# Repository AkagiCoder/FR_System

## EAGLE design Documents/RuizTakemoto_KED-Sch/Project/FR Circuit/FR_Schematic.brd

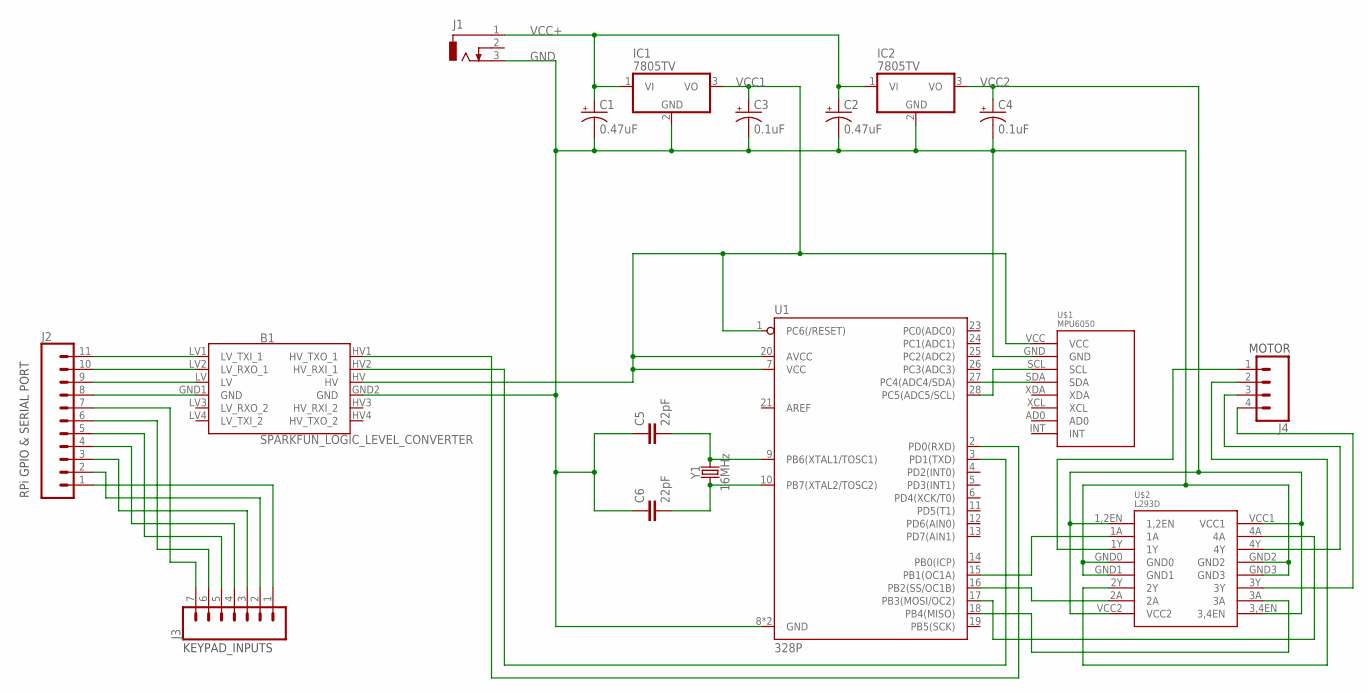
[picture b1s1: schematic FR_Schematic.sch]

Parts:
B1: SPARKFUN_LOGIC_LEVEL_CONVERTER
C1, C2: 0.47uF; CPOL-RADIAL-2.5MM-5MM
C3, C4: 0.1uF; E1,8-4
C5, C6: 22pF; CAP-PTH-2.54
IC1, IC2: 7805TV; TO220V
J1: DCJ0303
J2: CONN_11; 1X11
J3: CONN_07; 1X07
J4: CONN_04PTH; 1X04
U1: 328P; DIP28
U$1: MPU6050
U$2: L293D
Y1: 16MHz; HC49US

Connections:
GND: B1.GND2 (GND), C1.2 (-), C2.2 (-), C3.-, C4.-, C5.1, C6.1, IC1.2 (GND), IC2.2 (GND), J1.3, U1.8 (GND), U1.22 (GND), U$1.GND, U$2.GND0, U$2.GND1, U$2.GND2, U$2.GND3
unnamed: B1.HV1 (HV_TXO_1), U1.2 (PD0(RXD))
unnamed: B1.HV2 (HV_RXI_1), U1.3 (PD1(TXD))
unnamed: B1.LV1 (LV_TXI_1), J2.11
unnamed: B1.LV2 (LV_RXO_1), J2.10
unnamed: C6.2, U1.10 (PB7(XTAL2/TOSC2)), Y1.1
unnamed: C5.2, U1.9 (PB6(XTAL1/TOSC1)), Y1.2
unnamed: B1.LV, J2.9
unnamed: B1.GND1 (GND), J2.8
unnamed: J2.7, J3.7
unnamed: J2.6, J3.6
unnamed: J2.5, J3.5
unnamed: J2.4, J3.4
unnamed: J2.3, J3.3
unnamed: J2.2, J3.2
unnamed: J2.1, J3.1
unnamed: U1.27 (PC4(ADC4/SDA)), U$1.SDA
unnamed: U1.28 (PC5(ADC5/SCL)), U$1.SCL
unnamed: U1.15 (PB1(OC1A)), U$2.1A
unnamed: U1.16 (PB2(SS/OC1B)), U$2.2A
unnamed: U1.17 (PB3(MOSI/OC2)), U$2.4A
unnamed: U1.18 (PB4(MISO)), U$2.3A
unnamed: J4.1, U$2.1Y
unnamed: J4.2, U$2.2Y
unnamed: J4.3, U$2.4Y
unnamed: J4.4, U$2.3Y
VCC1: B1.HV, C3.+, IC1.3 (VO), U1.1 (PC6(/RESET)), U1.7 (VCC), U1.20 (AVCC), U$1.VCC
VCC2: C4.+, IC2.3 (VO), U$2.1,2EN, U$2.3,4EN, U$2.VCC1, U$2.VCC2
VCC+: C1.1 (+), C2.1 (+), IC1.1 (VI), IC2.1 (VI), J1.1

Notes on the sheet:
KEYPAD_INPUTS
RPi GPIO & SERIAL PORT
MOTOR

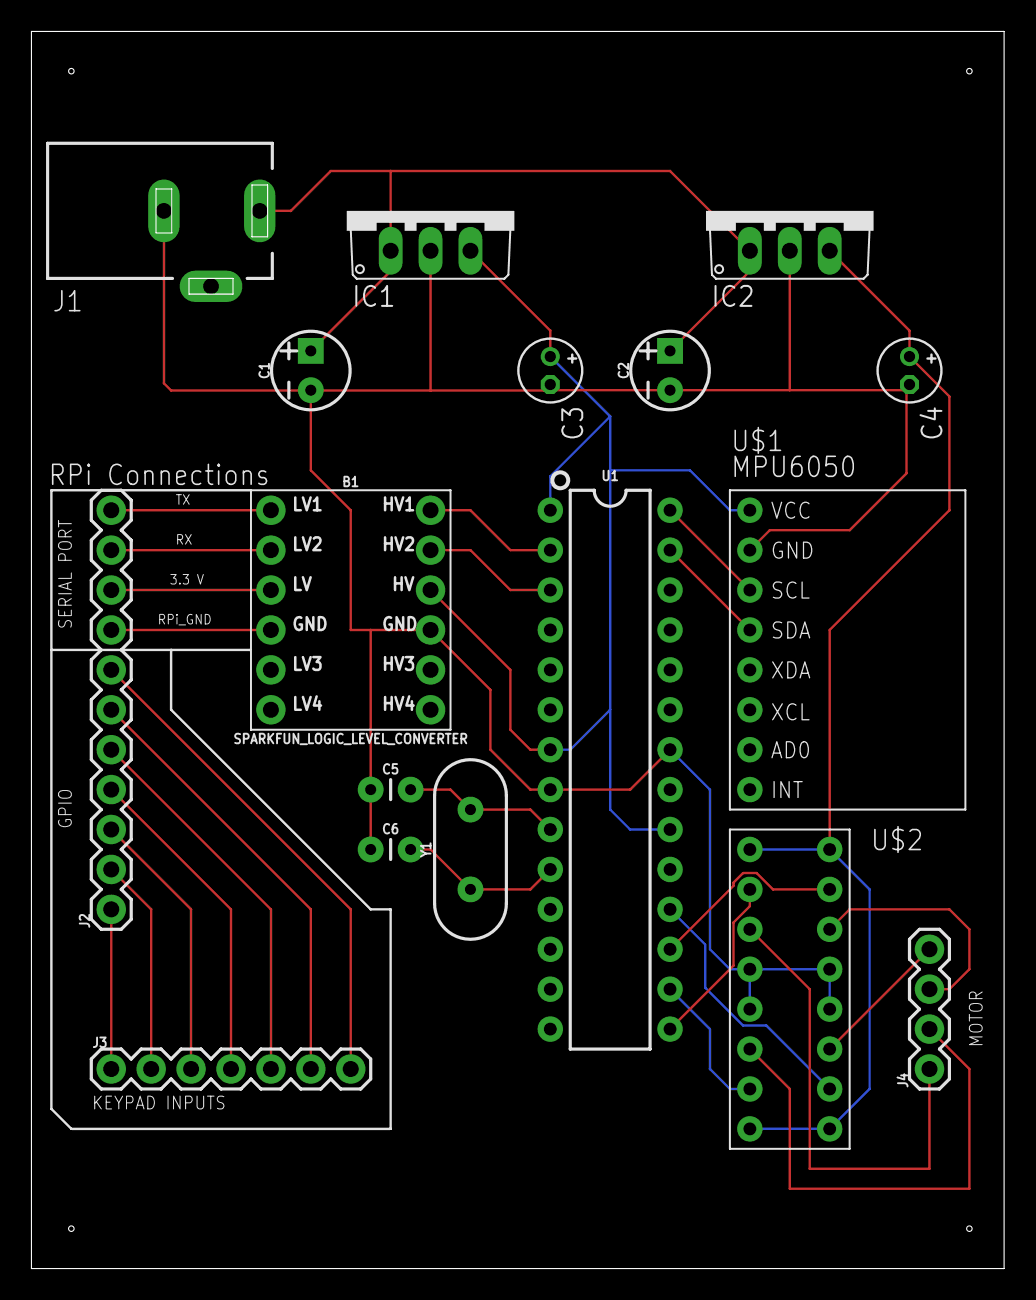
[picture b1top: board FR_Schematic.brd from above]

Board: 2 copper layers, 61.9 x 78.7 mm, 17 parts (0 on the bottom side), 29 nets.

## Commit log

2020-01-25 Added UART commands to motor
2020-01-28 Part lists
2020-01-28 Remove unnecessary test files
2020-01-28 Rearranged files into directories
2020-01-28 Update docs
2020-01-29 Added mutex to file and UART
2020-01-30 Updated the expired key checker thread function.
2020-01-31 Uploaded the ATmega source code
2020-01-31 Updated the progress list
2020-01-31 Cleaned up the main code
2020-01-31 Added datasheets
2020-01-31 Tested UART for MPU
    Got the ATmega to send MPU values for X-axis when requested by RPi.
2020-01-31 Tested the first retrieval of the accelerometer from ATmega to RPi for the X-axis. Need to create a thread to check acceleration and adjust the sensitivity.
2020-01-31 Ignore .DS_Store files
2020-02-01 Added syllabus
2020-02-01 Ignore backup files
2020-02-01 Halfway done with timeline
2020-02-01 Updated progress txt
2020-02-01 Added more stuff to the timeline
2020-02-01 Finished timeline
2020-02-01 Added Haar-Classifier stuff
2020-02-01 Added Molly's material
2020-02-01 Added purchased items
2020-02-02 FaceNet and Timeline
2020-02-02 Moved timeline to the correct place
2020-02-03 Little bit of the Molly Marks
2020-02-03 Updated Progress
2020-02-05 Finished Molly Marks Abstract, Up for Edit
2020-02-05 Added ATmega datasheet
2020-02-06 Added a keyList.dat check for main.py. Created requirement.txt
2020-02-06 Fixed a few instructions
2020-02-06 Ignore Main/__pycache/
2020-02-08 Specified instructions for configuring the RPi's serial port and added keyList.dat to ignore
2020-02-08 Updated keyList.dat
2020-02-08 Removed keyList from git
2020-02-09 Added a pinout diagram for RPi4
2020-02-09 Added complete support for MPU and its datasheet
2020-02-09 Fixed the UART and MPU bug
2020-02-10 Edited Molly Marks Abstract
2020-02-11 Updated ignore
2020-02-11 Added some tests
2020-02-11 Upload sch image
2020-02-11 Schematic Updated
2020-02-12 Added How tos
2020-02-14 Added more threads
2020-02-14 Test FR just Cam
2020-02-15 CNN added as Thread
2020-02-20 Modified the program
2020-02-20 Fixed a typo for picamera dependency
2020-02-21 Added Some to Progress
2020-02-21 2 Paragraphs
2020-02-22 Add abstract
2020-02-23 Revised Current State
2020-02-23 Revised Summary, and added to tabels
2020-02-24 There you go
2020-02-24 Fixed bullets
2020-02-24 Added dependency
2020-02-24 Working model
2020-02-24 Added classifier
2020-02-24 Cleaned up the code
2020-02-24 Removed old file
2020-02-24 Updated Deepface and ignore
2020-02-25 Added Facenet support
2020-02-25 Added more info
2020-02-25 Removed haar program
2020-02-25 Modified some code
2020-02-25 Final Report Initial
2020-02-25 Added citation
2020-02-26 weight link
2020-02-26 Added lock thread
2020-02-26 Layed out basics of the report
2020-02-28 Initial KED_GUI
2020-02-29 Removed tested GUI
2020-02-29 Removed KED_GUI
2020-03-01 Finished curses for menu
2020-03-01 added to introduction/background
2020-03-01 added face net cites
2020-03-01 V1 of reading the intro
2020-03-01 Finished porting keyGen to curses
2020-03-01 Ported key removal to curses
2020-03-02 Fully functional FNET
2020-03-04 Revised Intro in Versions1
2020-03-09 Email and Research added
2020-03-09 Removed my password
2020-03-14 Modified accel on python code
2020-03-15 changed accel
2020-03-15 Fixed the UART bug with accelerometer and started the alarm thread
2020-03-15 Set up the sensitivity settings
2020-03-16 ATmega now sends one string that contains XYZ accel.
2020-03-20 Revised Research
2020-03-31 Functionality/Arch/Design
2020-04-05 Keypad pin has been modified
2020-04-07 Almost finished the settings
2020-04-07 Removed old global vars from Settings
2020-04-14 Hope it doesn't break
2020-04-22 Poster added
2020-04-23 Highlighted source
2020-04-25 Flyer added
2020-04-26 Fixed the UART problem between door lock and MPU
2020-04-26 Working check for accelerometer
2020-04-27 Moved it
2020-04-28 Added More Securtity stf
2020-04-28 testing switch
2020-04-28 Added the reed switch and implemented security for break-in
2020-04-28 Added a simple alarm audio test using a song
2020-04-29 Implemented the alarm sound effect
2020-04-29 Started work on taking a picture of intruder
2020-05-02 added Use case pic
2020-05-02 moved images
2020-05-02 Added everything to the report
2020-05-03 Added stuff in my code
2020-05-03 Revised
2020-05-03 Added ignores to the image directories
2020-05-03 Implemented picture taking measures
2020-05-04 socket stuff
2020-05-04 Pushing up old stuff
2020-05-04 Set up a skeleton for photo booth
2020-05-05 photo booth
2020-05-05 Fixed the facial recognition
2020-05-05 Fixed conflict, successful merge
2020-05-05 updated the socket code
2020-05-06 Added Key Type, Socket for Key and Break in, and Email too
2020-05-06 Added Key Type, Key and Break in Socket, and Email
2020-05-06 Commented Code
2020-05-06 Updated requirement
2020-05-06 Removed old comments
2020-05-06 Added Selecting/Deleting Users
2020-05-06 Forgotten packages
2020-05-06 Commiting before pull
2020-05-07 Removed a junk file
2020-05-07 Moved stuff out
2020-05-07 Moved stuff new location
2020-05-07 Changed Adrian Pic
2020-05-07 Put the Deepface Module Back UP
2020-05-07 New pic
2020-05-07 New photo
2020-05-07 Modified code
2020-05-07 Deleted photos

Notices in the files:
parts and their libraries:
SparkFun-Boards: Licensing: Creative Commons ShareAlike 4.0 International - https://creativecommons.org/licenses/by-sa/4.0
